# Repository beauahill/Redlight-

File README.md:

# Redlight – ESP32 goal light

Firmware to bring a dead light-tower goal light (like the Bud Light Red Light)
back to life with an **ESP32-C3 or ESP32-C6**. When one of your favorite NHL
teams scores, it fires the tower's lights in sequence to make the rotating
strobe and plays a horn/siren through the original speaker. It runs off a **wall power supply** instead of
batteries, and there's no phone app: everything is set up from a web page the
light serves itself.

* Polls the public NHL score feed (`api-web.nhle.com`), every 5 s during
  your teams' games and slower otherwise
* Pick any number of favorite teams
* **TV delay** setting so the light goes off when *you* see the goal, not
  30 s early
* Plays your own `horn.wav` (upload it from the browser), or a built-in
  synthesized horn + siren if none is installed
* Goals that are overturned on review are handled, and goals scored
  before power-up are ignored
* Light patterns: **Lighthouse** (default: a narrow beam sweeps around the
  tower, one bank flashing after another), **Spin** (softer, with a fading
  tail), **Chase**, **Strobe**, **Alternate**, with adjustable speed and brightness

* The housing's original buttons: TEST to test/stop (hold 10 s to reset
  WiFi), VOL+ / VOL- to change the volume

Hardware and wiring: **[docs/WIRING.md](docs/WIRING.md)**

## Build & flash

Install [PlatformIO](https://platformio.org/install) (VS Code extension or CLI), then:

```bash
pio run -e esp32c3 -t upload     # ESP32-C3 (SuperMini, XIAO C3, DevKitM)
pio run -e esp32c6 -t upload     # ESP32-C6 DevKitC-1
pio run -e xiao_c6 -t upload     # Seeed XIAO ESP32-C6
pio device monitor               # serial log
```

If upload won't start, hold **BOOT** while plugging in USB.

The build uses USB-CDC for `Serial` (right for SuperMini/XIAO boards). On a
board whose USB goes through a UART chip, like the C3 DevKitM-1, remove
`-D ARDUINO_USB_CDC_ON_BOOT=1` to see logs.

## First-time setup

1. Power it up. It creates a WiFi network called **`GoalLight-Setup`**.
2. Join it from your phone. A captive portal opens (if not, browse to
   `192.168.4.1`). Choose your home WiFi and enter the password.
3. It reboots and joins your network. Open **http://goallight.local**
   (or the IP printed on the serial monitor / shown in your router).
4. Tick your teams, set the TV delay, and hit **Save**. Press **Test goal**.

## The horn sound

The original sound lived on the fried board, so you'll need to supply one:
a recording of a goal horn, your team's arena horn + goal song, etc. Convert
it and upload from the web page:

```bash
./tools/make_horn.sh goal-horn.mp3          # -> horn.wav (needs ffmpeg)
```

Any **16-bit PCM WAV** (mono or stereo, any sample rate) works. The filesystem
holds about 2 MB, roughly 45 s at the script's 22 kHz mono. The horn plays once
per goal, and the lights run for the **Light duration** setting.

## Syncing to your TV

Cable/satellite is typically 5–15 s behind the live feed and streaming
30–60 s or more. Leave the delay at 0 for one game and time how long it is
from the light going off to seeing the goal on your TV. Put that number in
**TV / stream delay**.

## Project layout

```
src/config.h      pins and defaults
src/main.cpp      WiFi setup, button, main loop
src/nhl.cpp       NHL score polling + goal detection
src/tower.cpp     light sequencing / patterns (runs in its own task)
src/celebrate.cpp goal celebration, WAV player, synth siren
src/web.cpp       settings page, status, WAV upload
src/settings.cpp  settings stored in flash (NVS)
docs/WIRING.md    parts list and schematic
tools/make_horn.sh audio conversion helper
```

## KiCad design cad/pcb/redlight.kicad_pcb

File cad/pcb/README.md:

# Replacement tower PCB (v2)

Drop-in replacement for the original "Red Light 2.0" board: same outline
(109.5 mm circle, 74.15 mm across the flats), a 4.2 mm tower screw hole, and
six slots for the 5.15 mm LED strip tabs.

The speaker sits only 11 mm below the board, so all tall parts go on the
**tower side**, which is hidden inside the housing. On that side the red glass
necks down to ~82 mm inside diameter 13 mm above the board, so anything
outside r = 41 mm is kept under 12 mm (`fit_stl.py` checks this). The tallest
part is the XIAO at ~9.5 mm. The speaker side carries
only the angled TEST switch (~4 mm) and solder pads for wires.

## Files

| File | What |
|---|---|
| `redlight-gerbers.zip` | upload this to JLCPCB / PCBWay / OSH Park |
| `redlight.kicad_pcb` | KiCad board (opens in KiCad 7, 8, 9) |
| `out/redlight_fit.stl` | printable fit model (tower-side parts as blocks of real size/height) |
| `make_pcb.py` | generates the board: outline, slots, placement, nets |
| `route.py` | autoroutes (Freerouting), pours ground, DRC, Gerbers |
| `fit_stl.py` | builds the fit model from the board |

There's no schematic sheet. The netlist is defined in `make_pcb.py`, and
`docs/WIRING.md` has the circuit.

## Ordering

JLCPCB settings that were checked for this board: FR-4, 2 layers, 1.6 mm,
1 oz, HASL, tented vias, 0.3 mm min via, ±0.2 mm outline tolerance, single
PCB, no assembly. Color is free choice. The six tab slots are 5.7 × 1.25 mm;
the extra length covers the router's rounded slot ends.

2 layers, 1.6 mm, any color, HASL (lead-free is fine), 1 oz copper.
The six tab slots and the screw hole are cut from the Edge.Cuts outline
(non-plated), which every fab handles at no extra cost. Leave other options
at their defaults.

## Parts (BOM)

| Ref | Part | Notes |
|---|---|---|
| U1 | Seeed XIAO ESP32-C6 | on 2× 1x7 **low-profile** female headers (≤ 5 mm), or soldered straight onto male pins. Standard 8.5 mm sockets are too tall for the glass |
| U2 | TBD62083APG | DIP-18, in a DIP-18 socket. ULN2803A also fits (dimmer) |
| R1–R6 | wire jumpers (0 Ω) | each strip has its own 20 Ω resistor ("200"). Use a clipped lead; the pads take a 1/4 W axial resistor if you ever want to dim a strip |
| R7, R8 | 100 kΩ 1/4 W axial | battery gauge divider |
| C1 | 220 µF 10 V electrolytic, 6.3 mm dia, 2.5 mm pitch, up to 6.3 × 11 mm | e.g. Rubycon 10YXS220MEFC6.3X11 (Digi-Key 1189-10YXS220MEFC6.3X11-ND). Sits inside the glass neck, so 12.5 mm tall is fine. Watch polarity |
| C2 | 100 nF (0.1 µF) ceramic, 50 V, 5.08 mm pitch | e.g. KEMET C322C104K5R5TA. The C320C104K5R5TA (Digi-Key 399-4264-ND) also works with its 2.54 mm leads spread slightly |
| J1 | solder pads, 3-way (speaker side) | 5V / GND / VBAT wires from the UPS module + cells |
| J2 | solder pads, 2-way (speaker side) | optional external TEST button |
| J3 | (holes only) | MAX98357A breakout soldered straight on its 1x7 male header, components facing away |
| SW1–SW3 | PTS645 right-angle 6 mm tact switch (speaker side) | TEST, VOL+, VOL- at the housing's buttons |
| R10, R11, R12 | 10 kΩ, 2.2 kΩ, 6.8 kΩ 1/4 W axial | button resistor ladder |
| — | MAX98357A breakout (Adafruit 3006 or clone) | **leave the screw terminal off**; solder the speaker wires to its + / − pads |

## Final check (before ordering)

* Netlist dumped from the board and compared against the firmware pin map
  (`src/config.h`): every XIAO pin, lights 1-6 in order around the tower,
  I2S, button ladder, battery sense.
* XIAO ESP32-C6 D-pin to GPIO mapping and TBD62083APG pinout (pin 9 GND,
  pin 10 COMMON) confirmed against published pinouts / the Toshiba datasheet.
* DRC: no copper errors, no unconnected pads. Fit prints checked in the housing.
* Not verifiable here: the MAX98357A module's orientation on J3. J3 has the
  pin names printed beside it; line them up with the module's labels before
  soldering (mount it upside down if that's what makes them match).

## Before ordering

- [x] Flat fit print: outline, tab slots, screw hole
- [x] Fit print v3 (no support tab): outline, slots, screw hole, parts clearance
- [ ] v2 fit print: tower-side parts clear the dome, tab sits in the recess
- [x] Tab thickness 1.0 mm, width 5.15 mm; strip inside faces 13.6 mm across (slot centers at r = 7.3 mm)
- [x] "+" is the counter-clockwise half of each tab from the tower side (checked on the fit print)
- [x] Button positions (TEST 39.6 mm, VOL± 48 mm and 20.15 mm apart)
- [x] Strips run on 5 V (very bright on the bench supply); worst case ~160 mA each

To regenerate after a change:

```bash
python3 cad/pcb/make_pcb.py
FREEROUTING_JAR=~/freerouting-1.9.0.jar python3 cad/pcb/route.py   # needs Java (+ xvfb-run on headless Linux)
python3 cad/pcb/fit_stl.py
```

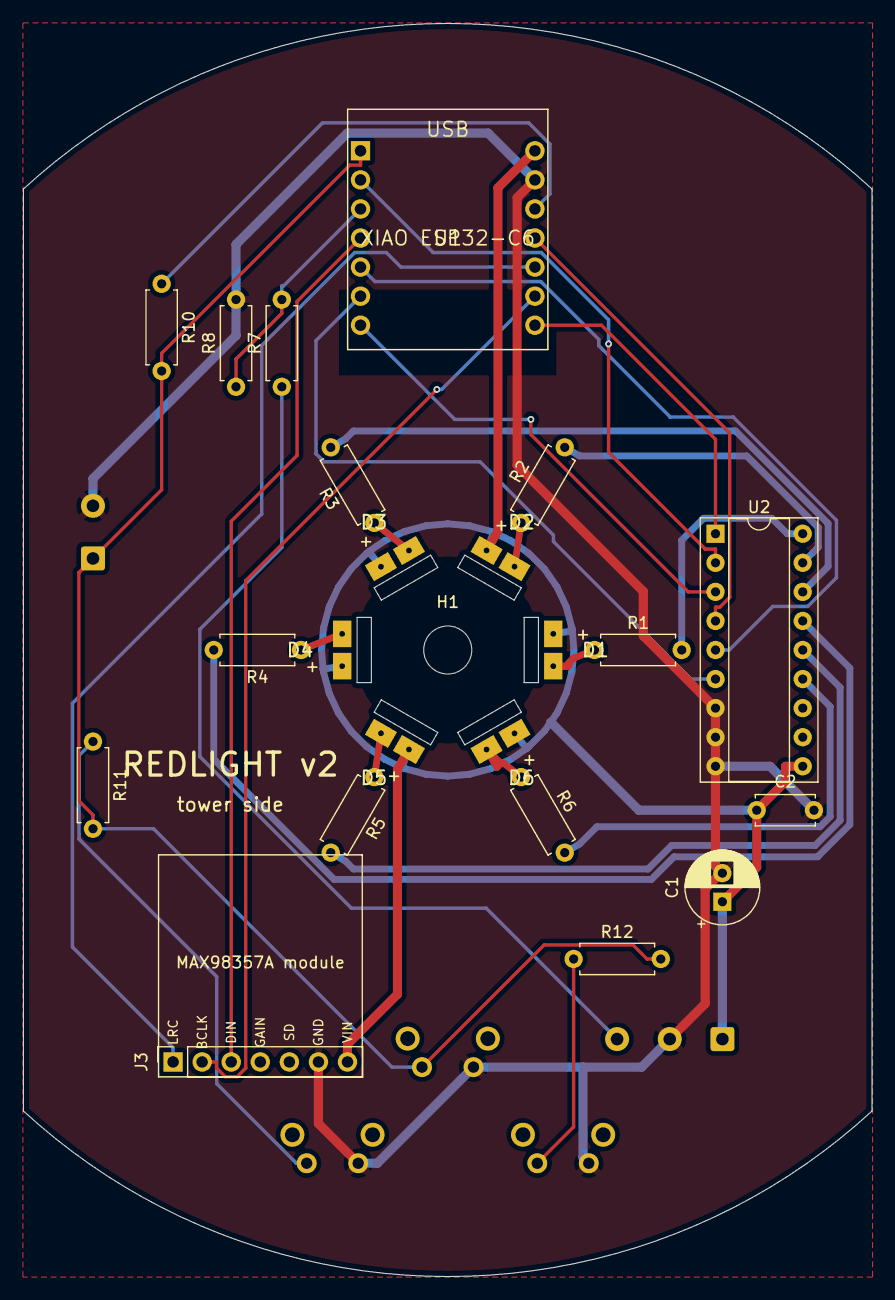
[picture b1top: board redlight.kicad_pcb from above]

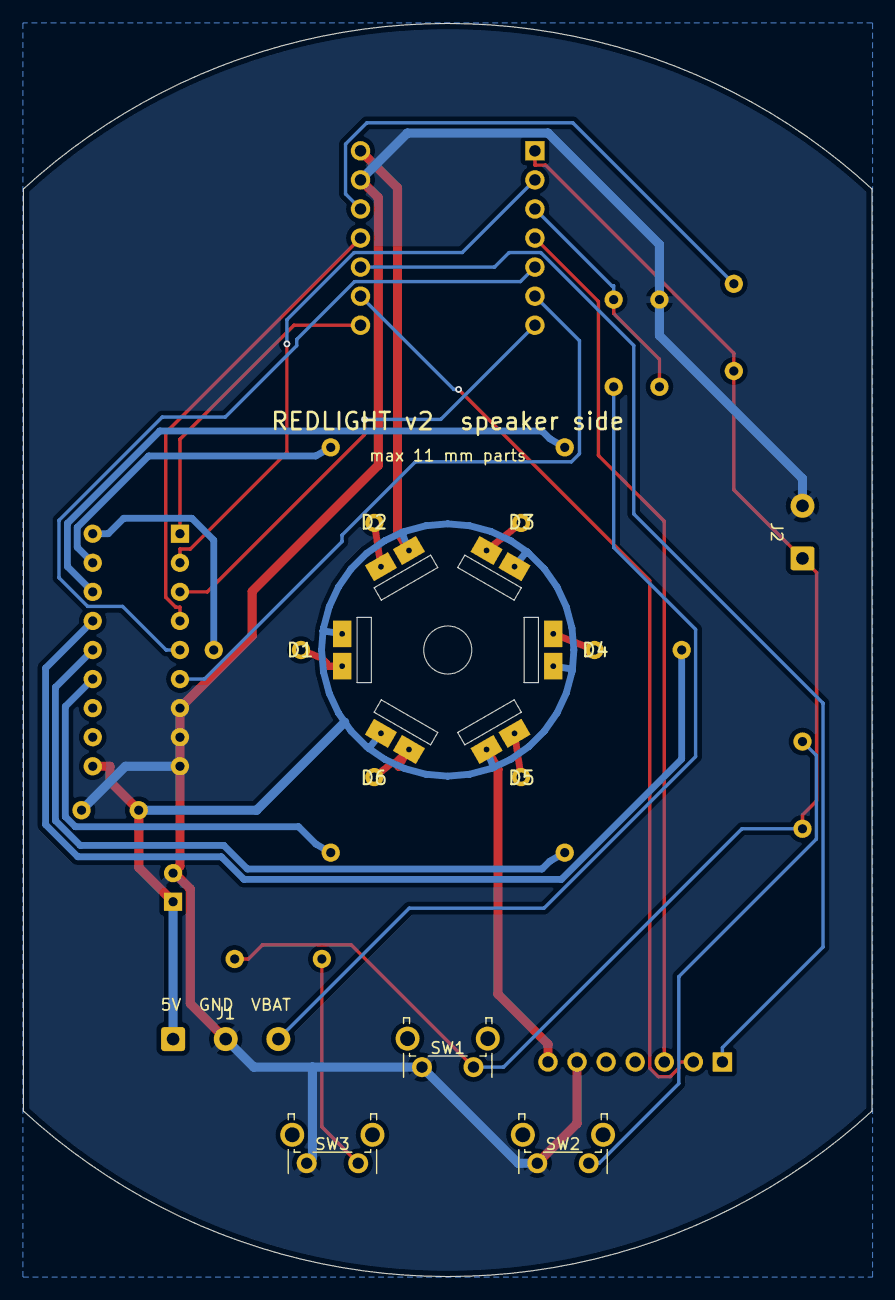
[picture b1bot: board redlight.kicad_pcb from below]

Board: 2 copper layers, 74.1 x 109.5 mm, 28 parts (5 on the bottom side), 29 nets.

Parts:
C1: 220uF 10V 6.3x7; CP_Radial_D6.3mm_P2.50mm
C2: 100nF; C_Disc_D5.0mm_W2.5mm_P5.00mm
H1: tower screw; MountingHole_3.2mm_M3
J1: 5V GND VBAT; SolderWire-0.5sqmm_1x03_P4.6mm_D0.9mm_OD2.1mm
J2: EXT TEST; SolderWire-0.5sqmm_1x02_P4.6mm_D0.9mm_OD2.1mm
J3: MAX98357A; PinSocket_1x07_P2.54mm_Vertical
LED1, LED2, LED3, LED4, LED5, LED6: strip tab
R1, R2, R3, R4, R5, R6: 0R; R_Axial_DIN0207_L6.3mm_D2.5mm_P7.62mm_Horizontal
R7, R8: 100k; R_Axial_DIN0207_L6.3mm_D2.5mm_P7.62mm_Horizontal
R10: 10k; R_Axial_DIN0207_L6.3mm_D2.5mm_P7.62mm_Horizontal
R11: 2k2; R_Axial_DIN0207_L6.3mm_D2.5mm_P7.62mm_Horizontal
R12: 6k8; R_Axial_DIN0207_L6.3mm_D2.5mm_P7.62mm_Horizontal
SW1: TEST; SW_Tactile_SPST_Angled_PTS645Vx31-2LFS
SW2: VOL+; SW_Tactile_SPST_Angled_PTS645Vx31-2LFS
SW3: VOL-; SW_Tactile_SPST_Angled_PTS645Vx31-2LFS
U1: XIAO ESP32-C6
U2: TBD62083APG; DIP-18_W7.62mm_Socket

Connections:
+3V3: R10.1, U1.3V3
+5V: C1.1, C2.1, J1.1, J3.7, LED1.+, LED2.+, LED3.+, LED4.+, LED5.+, LED6.+, U1.5V, U2.10
/BUTTONS: J2.1, R10.2, R11.2, R12.2, SW1.1, U1.D0
/I2S_BCLK: J3.2, U1.D8
/I2S_DIN: J3.3, U1.D3
/I2S_LRC: J3.1, U1.D9
/LIGHT1: U1.D7, U2.1
/LIGHT2: U1.D1, U2.2
/LIGHT3: U1.D6, U2.3
/LIGHT4: U1.D10, U2.4
/LIGHT5: U1.D4, U2.5
/LIGHT6: U1.D5, U2.6
/OUT1: R1.2, U2.18
/OUT2: R2.2, U2.17
/OUT3: R3.2, U2.16
/OUT4: R4.2, U2.15
/OUT5: R5.2, U2.14
/OUT6: R6.2, U2.13
/STRIP1-: LED1.-, R1.1
/STRIP2-: LED2.-, R2.1
/STRIP3-: LED3.-, R3.1
/STRIP4-: LED4.-, R4.1
/STRIP5-: LED5.-, R5.1
/STRIP6-: LED6.-, R6.1
/VBAT: J1.3, R7.1
/VOL+: R11.1, SW2.1
/VOL-: R12.1, SW3.1
/VSENSE: R7.2, R8.1, U1.D2
GND: C1.2, C2.2, J1.2, J2.2, J3.6, R8.2, SW1.2, SW2.2, SW3.2, U1.GND, U2.7, U2.8, U2.9
